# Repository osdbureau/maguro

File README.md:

# maguro
Maguro Game Controller

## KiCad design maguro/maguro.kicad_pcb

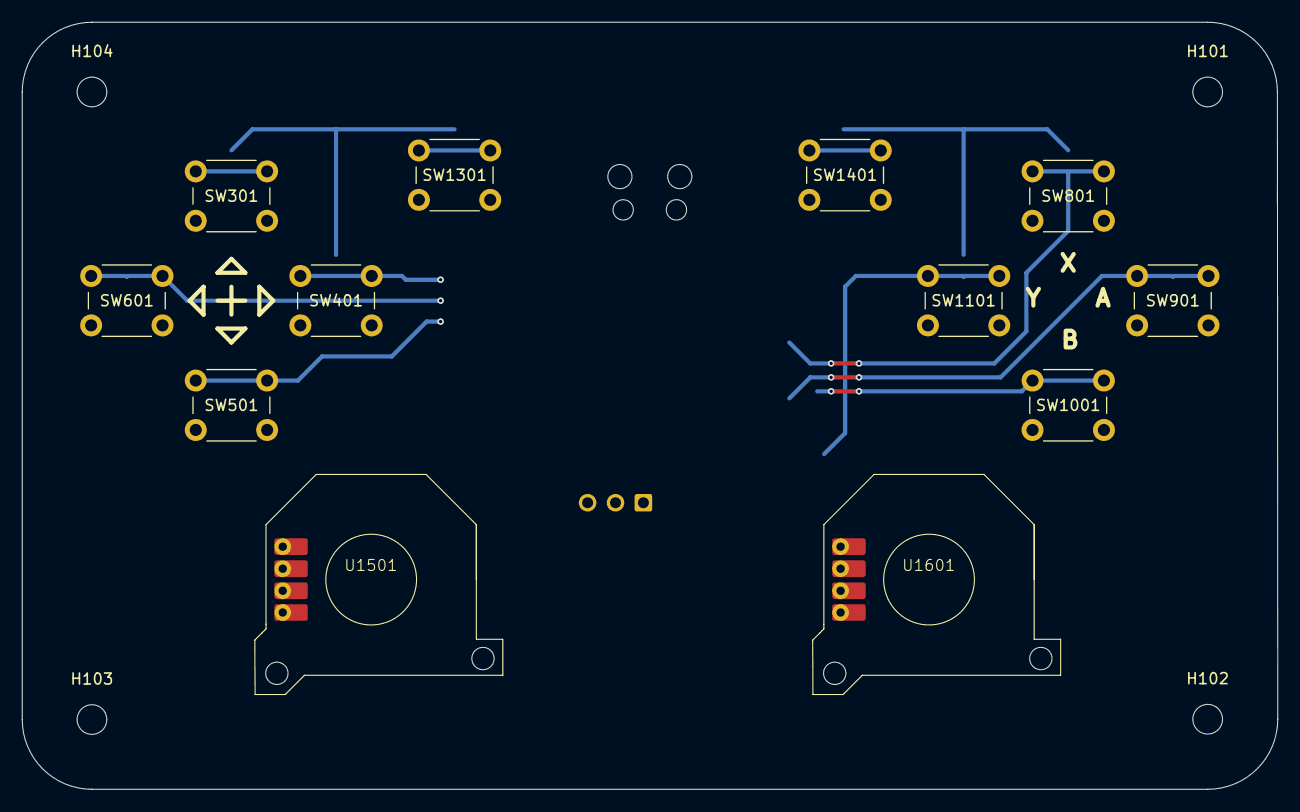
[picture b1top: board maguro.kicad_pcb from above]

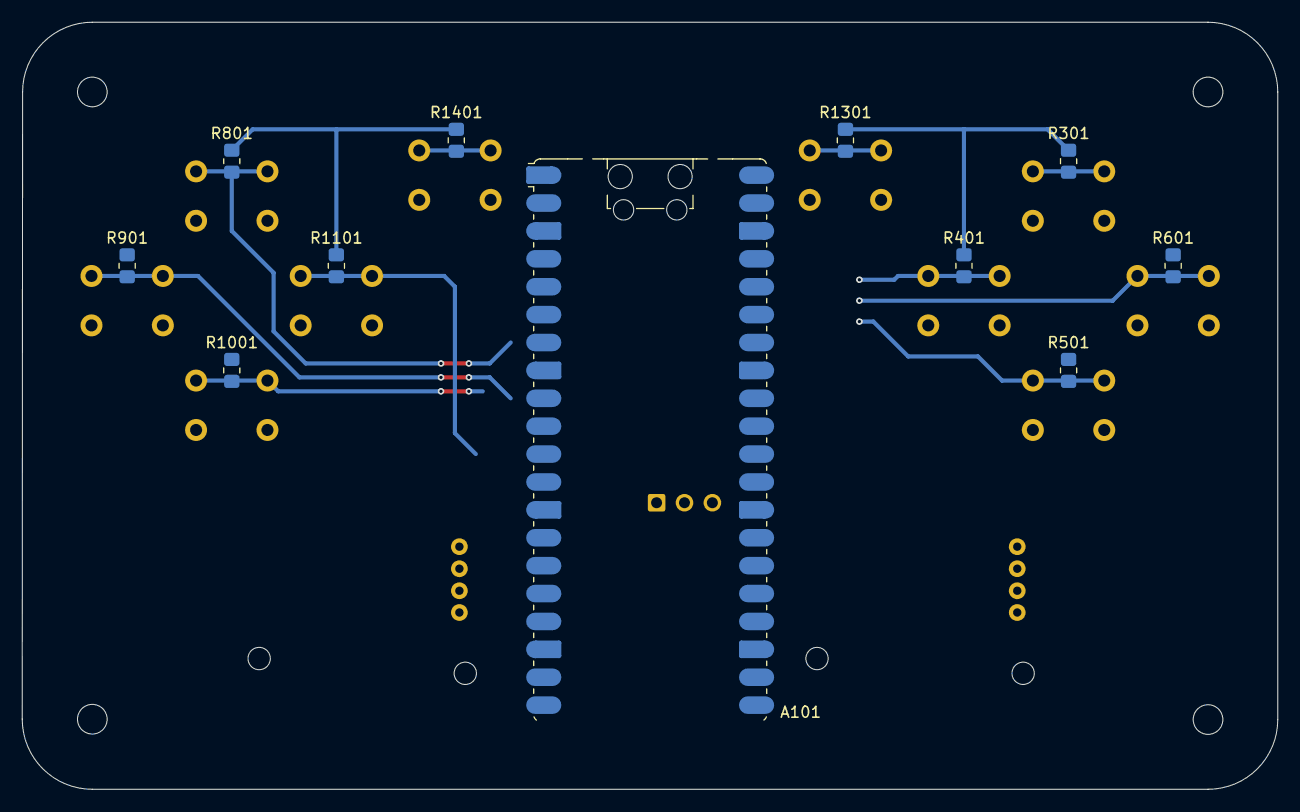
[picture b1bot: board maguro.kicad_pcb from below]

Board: 2 copper layers, 114.3 x 69.8 mm, 27 parts (11 on the bottom side), 13 nets.

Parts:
A101: RaspberryPi_Pico_W; RaspberryPi_Pico_W_SMD_HandSolder
H101, H102, H103, H104: MountingHole; MountingHole_2.7mm_M2.5
R301, R401, R501, R601, R801, R901, R1001, R1101, R1301, R1401: R_US; R_0805_2012Metric_Pad1.20x1.40mm_HandSolder
SW301, SW401, SW501, SW601, SW801, SW901, SW1001, SW1101, SW1301, SW1401: SW_Push; SW_PUSH_6mm_H8mm
U1501, U1601: COM-09426

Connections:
+3V3: R301.1, R401.1, R501.1, R601.1, R801.1, R901.1, R1001.1, R1101.1, R1301.1, R1401.1, U1501.2 (V_in), U1601.2 (V_in)
/button_a: A101.14 (GPIO10), R901.2, SW901.1
/button_b: A101.15 (GPIO11), R1001.2, SW1001.1
/button_select: A101.5 (GPIO3), R1401.2, SW1401.1
/button_start: A101.4 (GPIO2), R1301.2, SW1301.1
/button_x: A101.12 (GPIO9), R801.2, SW801.1
/button_y: A101.16 (GPIO12), R1101.2, SW1101.1
/dpad_down: A101.10 (GPIO7), R601.2, SW601.1
/dpad_left: A101.11 (GPIO8), R501.2, SW501.1
/dpad_right: A101.9 (GPIO6), R401.2, SW401.1
/dpad_up: A101.7 (GPIO5), R301.2, SW301.1
GND: SW301.2, SW401.2, SW501.2, SW601.2, SW801.2, SW901.2, SW1001.2, SW1101.2, SW1301.2, SW1401.2, U1501.4 (GND), U1601.4 (GND)
unnamed: A101.3 (GND), A101.8 (GND), A101.13 (GND), A101.18 (GND), A101.23 (GND), A101.28 (GND), A101.38 (GND), A101.D2 (GND)

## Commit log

2025-03-16 Made resistor labels easier to read
2025-03-16 Pushed buttons to top
2025-03-16 Added joysticks
2025-03-16 Added thumbstick step
2025-03-16 Added silkscreen
